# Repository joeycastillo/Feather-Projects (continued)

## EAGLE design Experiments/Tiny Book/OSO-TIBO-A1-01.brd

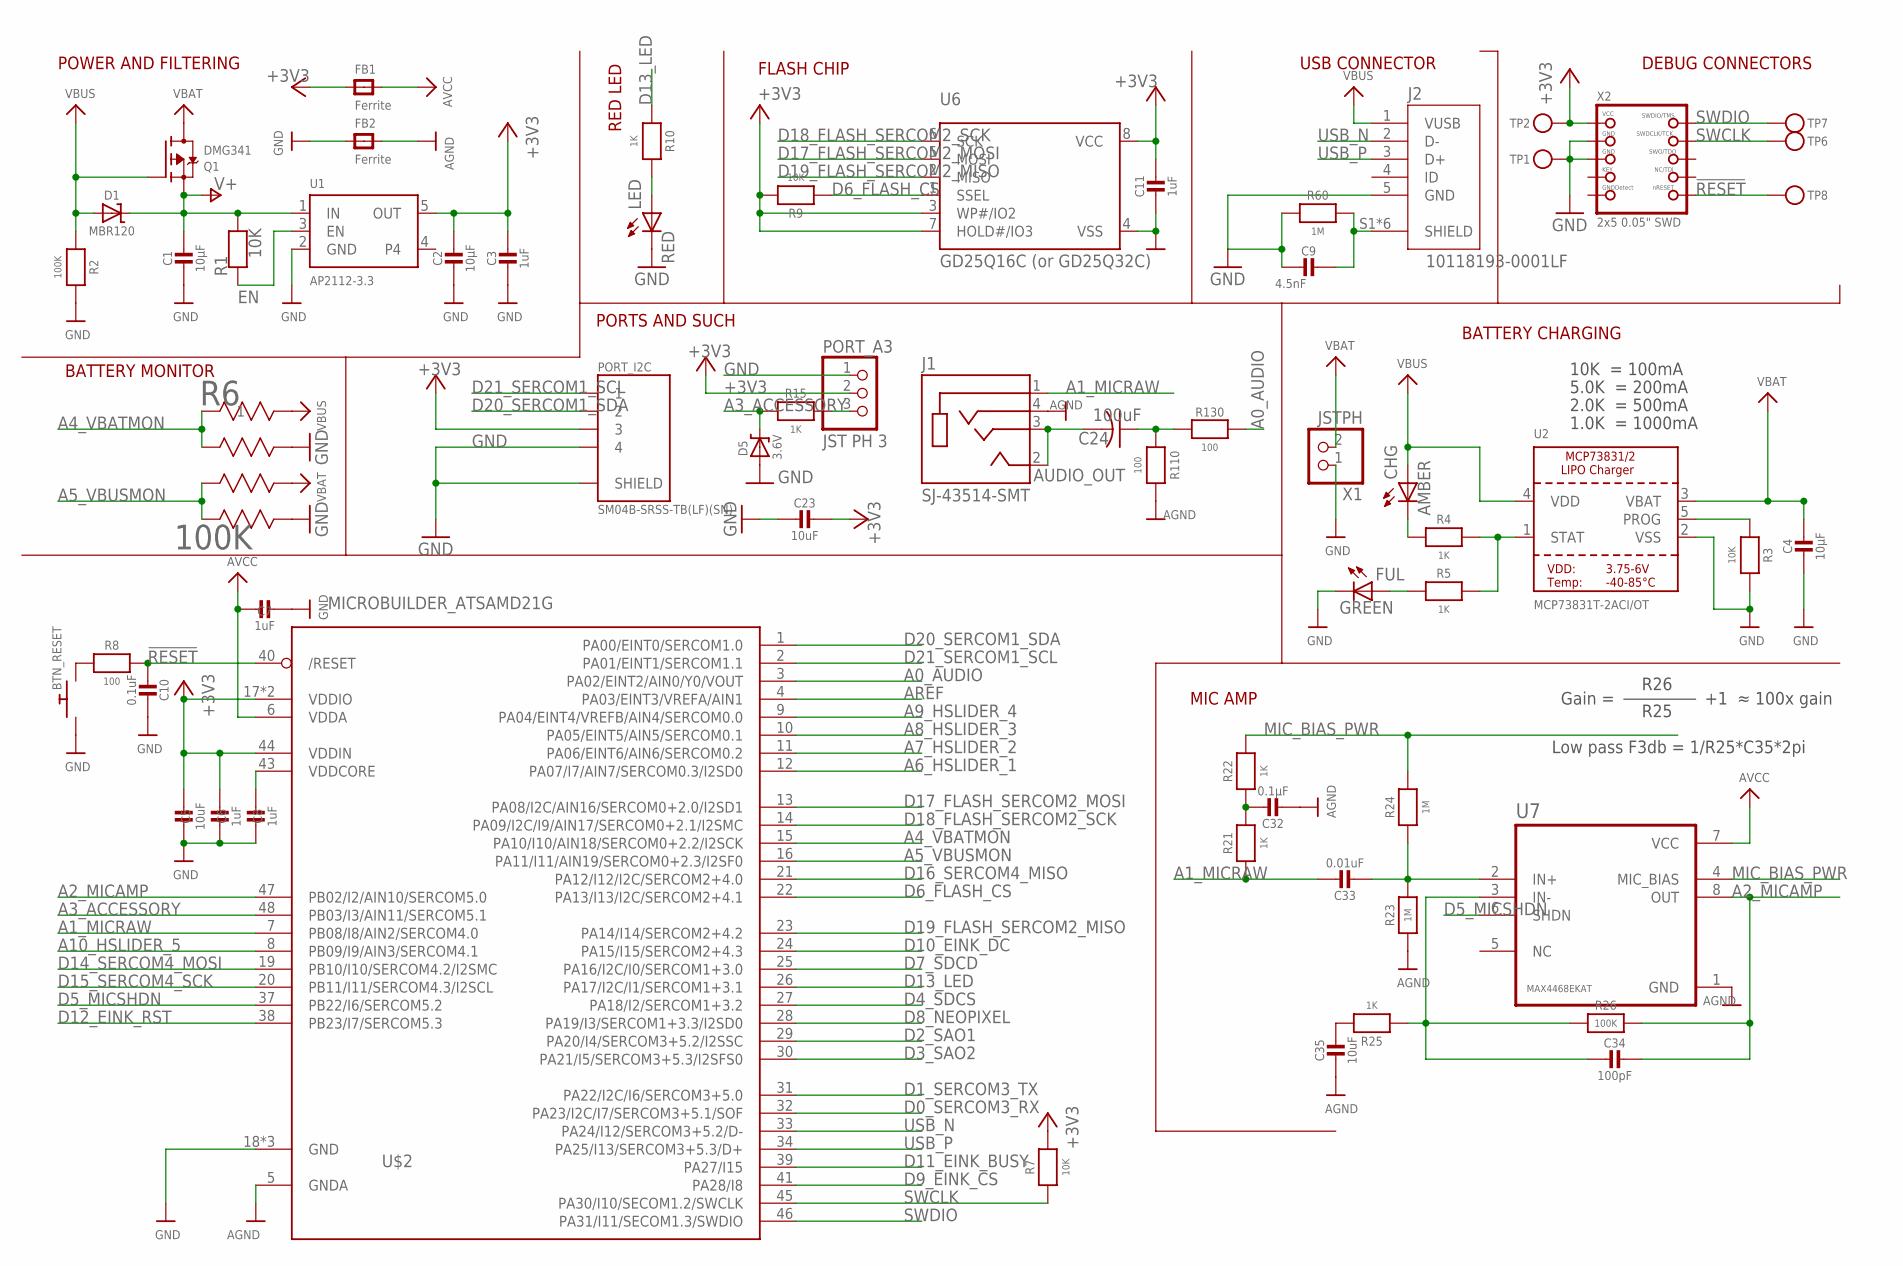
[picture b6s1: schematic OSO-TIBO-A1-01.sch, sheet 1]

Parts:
BTN_RESET: SPST_TACTILE_SWITCHRA-THRU; MJTP1117
C1, C2, C4: 10µF; 0805-NO
C3, C6, C7, C8: 1uF; 0805-NO
C5: 10uF; 0805_10MGAP
C9: 4.5nF; 0805-NO
C10: 0.1uF; 0805_10MGAP
C11: 1uF; 0805_10MGAP
C23, C35: 10uF; 0805-NO
C24: 100uF; C1210
C32: 0.1µF; 0805-NO
C33: 0.01uF; 0805-NO
C34: 100pF; 0805-NO
CHG: AMBER; CHIP-LED0805
D1: MBR120; SOD-123
D5: 3.6V; SOD-123
FB1, FB2: Ferrite; 0805
FUL: GREEN; CHIP-LED0805
J1: SJ-43514-SMT; CUI_SJ-43514-SMT
J2: 10118193-0001LF; FCI_10118193-0001LF
LED: RED; CHIP-LED0805
PORT_A3: JST PH 3; JSTPH3
PORT_I2C: SM04B-SRSS-TB(LF)(SN); JST_SM04B-SRSS-TB(LF)(SN)
Q1: DMG341; SOT23-R
R1, R3, R7, R9: 10K; 0805-NO
R2, R26: 100K; 0805-NO
R4, R5, R10, R21, R22, R25: 1K; 0805-NO
R6: 100K; EXBV8V
R8: 100; 0805_10MGAP
R15: 1K; _0805MP
R23, R24, R60: 1M; 0805-NO
R110, R130: 100; 0805-NO
TP1, TP2, TP6, TP7, TP8: TESTPOINTROUND2MMNO; TESTPOINT_ROUND_2MM_NO
U1: AP2112-3.3; SOT23-5
U2: MCP73831T-2ACI/OT; SOT23-5
U6: GD25Q16C (or GD25Q32C); MICROBUILDER_SOIC8_150MIL
U7: MAX4468EKAT; SOT65P280X145-8N
U$2: MICROBUILDER_ATSAMD21G; QFP50P900X900X120-48N
X1: JSTPH; JSTPH2
X2: 2x5 0.05" SWD; 2X05_1.27MM_BOX_POSTS

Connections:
!RESET: C10.2, R8.2, TP8.P$1, U$2.40 (/RESET), X2.10 (NRESET)
+3V3: C2.1, C3.1, C5.1, C6.1, C11.1, C23.1, FB1.1, PORT_A3.2, PORT_I2C.3, R7.2, R9.2, TP2.P$1, U1.5 (OUT), U6.3 (WP#/IO2), U6.7 (HOLD#/IO3), U6.8 (VCC), U$2.17 (VDDIO), U$2.36 (VDDIO), U$2.44 (VDDIN), X2.1 (VCC); also elsewhere on the board
A0_AUDIO: R130.1, U$2.3 (PA02/EINT2/AIN0/Y0/VOUT)
A1_MICRAW: C33.1, J1.1 (SLEEVE), R21.1, U$2.7 (PB08/I8/AIN2/SERCOM4.0)
A2_MICAMP: C34.1, R26.2, U7.8 (OUT), U$2.47 (PB02/I2/AIN10/SERCOM5.0)
A3_ACCESSORY: D5.C, R15.2, U$2.48 (PB03/I3/AIN11/SERCOM5.1)
A4_VBATMON: R6.1, R6.2, U$2.15 (PA10/I10/AIN18/SERCOM0+2.2/I2SCK)
A5_VBUSMON: R6.3, R6.4, U$2.16 (PA11/I11/AIN19/SERCOM0+2.3/I2SF0)
A6_HSLIDER_1: U$2.12 (PA07/I7/AIN7/SERCOM0.3/I2SD0); also elsewhere on the board
A7_HSLIDER_2: U$2.11 (PA06/EINT6/AIN6/SERCOM0.2); also elsewhere on the board
A8_HSLIDER_3: U$2.10 (PA05/EINT5/AIN5/SERCOM0.1); also elsewhere on the board
A9_HSLIDER_4: U$2.9 (PA04/EINT4/VREFB/AIN4/SERCOM0.0); also elsewhere on the board
A10_HSLIDER_5: U$2.8 (PB09/I9/AIN3/SERCOM4.1); also elsewhere on the board
AGND: C32.2, C35.2, FB2.2, J1.4 (RING2), R23.1, R110.1, U7.1 (GND), U$2.5 (GNDA)
AREF: U$2.4 (PA03/EINT3/VREFA/AIN1)
AUDIO_OUT: C24.2, J1.2 (TIP), J1.3 (RING1)
AVCC: C7.2, FB1.2, U7.7 (VCC), U$2.6 (VDDA)
D0_SERCOM3_RX: U$2.32 (PA23/I2C/I7/SERCOM3+5.1/SOF); also elsewhere on the board
D1_SERCOM3_TX: U$2.31 (PA22/I2C/I6/SERCOM3+5.0); also elsewhere on the board
D2_SAO1: U$2.29 (PA20/I4/SERCOM3+5.2/I2SSC)
D3_SAO2: U$2.30 (PA21/I5/SERCOM3+5.3/I2SFS0)
D4_SDCS: U$2.27 (PA18/I2/SERCOM1+3.2); also elsewhere on the board
D5_MICSHDN: U7.6 (SHDN), U$2.37 (PB22/I6/SERCOM5.2)
D6_FLASH_CS: R9.1, U6.1 (SSEL), U$2.22 (PA13/I13/I2C/SERCOM2+4.1)
D7_SDCD: U$2.25 (PA16/I2C/I0/SERCOM1+3.0); also elsewhere on the board
D8_NEOPIXEL: U$2.28 (PA19/I3/SERCOM1+3.3/I2SD0); also elsewhere on the board
D9_EINK_CS: U$2.41 (PA28/I8); also elsewhere on the board
D10_EINK_DC: U$2.24 (PA15/I15/SERCOM2+4.3); also elsewhere on the board
D11_EINK_BUSY: U$2.39 (PA27/I15); also elsewhere on the board
D12_EINK_RST: U$2.38 (PB23/I7/SERCOM5.3); also elsewhere on the board
D13_LED: R10.1, U$2.26 (PA17/I2C/I1/SERCOM1+3.1)
D14_SERCOM4_MOSI: U$2.19 (PB10/I10/SERCOM4.2/I2SMC); also elsewhere on the board
D15_SERCOM4_SCK: U$2.20 (PB11/I11/SERCOM4.3/I2SCL); also elsewhere on the board
D16_SERCOM4_MISO: U$2.21 (PA12/I12/I2C/SERCOM2+4.0); also elsewhere on the board
D17_FLASH_SERCOM2_MOSI: U6.5 (MOSI), U$2.13 (PA08/I2C/AIN16/SERCOM0+2.0/I2SD1)
D18_FLASH_SERCOM2_SCK: U6.6 (SCK), U$2.14 (PA09/I2C/I9/AIN17/SERCOM0+2.1/I2SMC)
D19_FLASH_SERCOM2_MISO: U6.2 (MISO), U$2.23 (PA14/I14/SERCOM2+4.2)
D20_SERCOM1_SDA: PORT_I2C.2, U$2.1 (PA00/EINT0/SERCOM1.0)
D21_SERCOM1_SCL: PORT_I2C.1, U$2.2 (PA01/EINT1/SERCOM1.1)
EN: R1.1, U1.3 (EN); also elsewhere on the board
GND: BTN_RESET.P$1, C1.2, C2.2, C3.2, C4.2, C5.2, C6.2, C7.1, C8.2, C9.2, C10.1, C11.2, C23.2, D5.A, FB2.1, FUL.C, J2.5 (GND), LED.C, PORT_A3.1, PORT_I2C.4, PORT_I2C.S1 (SHIELD), PORT_I2C.S2 (SHIELD), R2.2, R3.2, R6.5, R6.7, R60.2, TP1.P$1, U1.2 (GND), U2.2 (VSS), U6.4 (VSS), U$2.18 (GND), U$2.35 (GND), U$2.42 (GND), X1.1, X2.3 (GND), X2.5 (GND); also elsewhere on the board
MIC_BIAS_PWR: R22.2, R24.2, U7.4 (MIC_BIAS)
unnamed: BTN_RESET.P$2, R8.1
unnamed: CHG.C, R4.1
unnamed: C24.1, R110.2, R130.2
unnamed: LED.A, R10.2
unnamed: FUL.A, R5.1
unnamed: C32.1, R21.2, R22.1
unnamed: C33.2, R23.2, R24.1, U7.2 (IN+)
unnamed: C34.2, R25.1, R26.1, U7.3 (IN-)
unnamed: C35.1, R25.2
PROG: R3.1, U2.5 (PROG)
SHIELD: C9.1, J2.S1 (SHIELD), J2.S2 (SHIELD), J2.S3 (SHIELD), J2.S4 (SHIELD), J2.S5 (SHIELD), J2.S6 (SHIELD), R60.1
STAT: R4.2, R5.2, U2.1 (STAT)
SWCLK: R7.1, TP6.P$1, U$2.45 (PA30/I10/SECOM1.2/SWCLK), X2.4 (SWDCLK)
SWDIO: TP7.P$1, U$2.46 (PA31/I11/SECOM1.3/SWDIO), X2.2 (SWDIO)
USB_N: J2.2 (D-), U$2.33 (PA24/I12/SERCOM3+5.2/D-)
USB_P: J2.3 (D+), U$2.34 (PA25/I13/SERCOM3+5.3/D+)
V+: C1.1, D1.C, Q1.2 (S), R1.2, U1.1 (IN)
VBAT: C4.1, Q1.3 (D), R6.6, U2.3 (VBAT), X1.2
VBUS: CHG.A, D1.A, J2.1 (VUSB), Q1.1 (G), R2.1, R6.8, U2.4 (VDD)
VDDCORE: C8.1, U$2.43 (VDDCORE)
_ACCESSORY: PORT_A3.3, R15.1

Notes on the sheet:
POWER AND FILTERING
10K = 100mA
5.0K = 200mA
2.0K = 500mA
1.0K = 1000mA
BATTERY CHARGING
DEBUG CONNECTORS
USB CONNECTOR
BATTERY MONITOR
FLASH CHIP
RED LED
Gain =
R26
R25
≈ 100x gain
Low pass F3db = 1/R25*C35*2pi
PORTS AND SUCH
MIC AMP

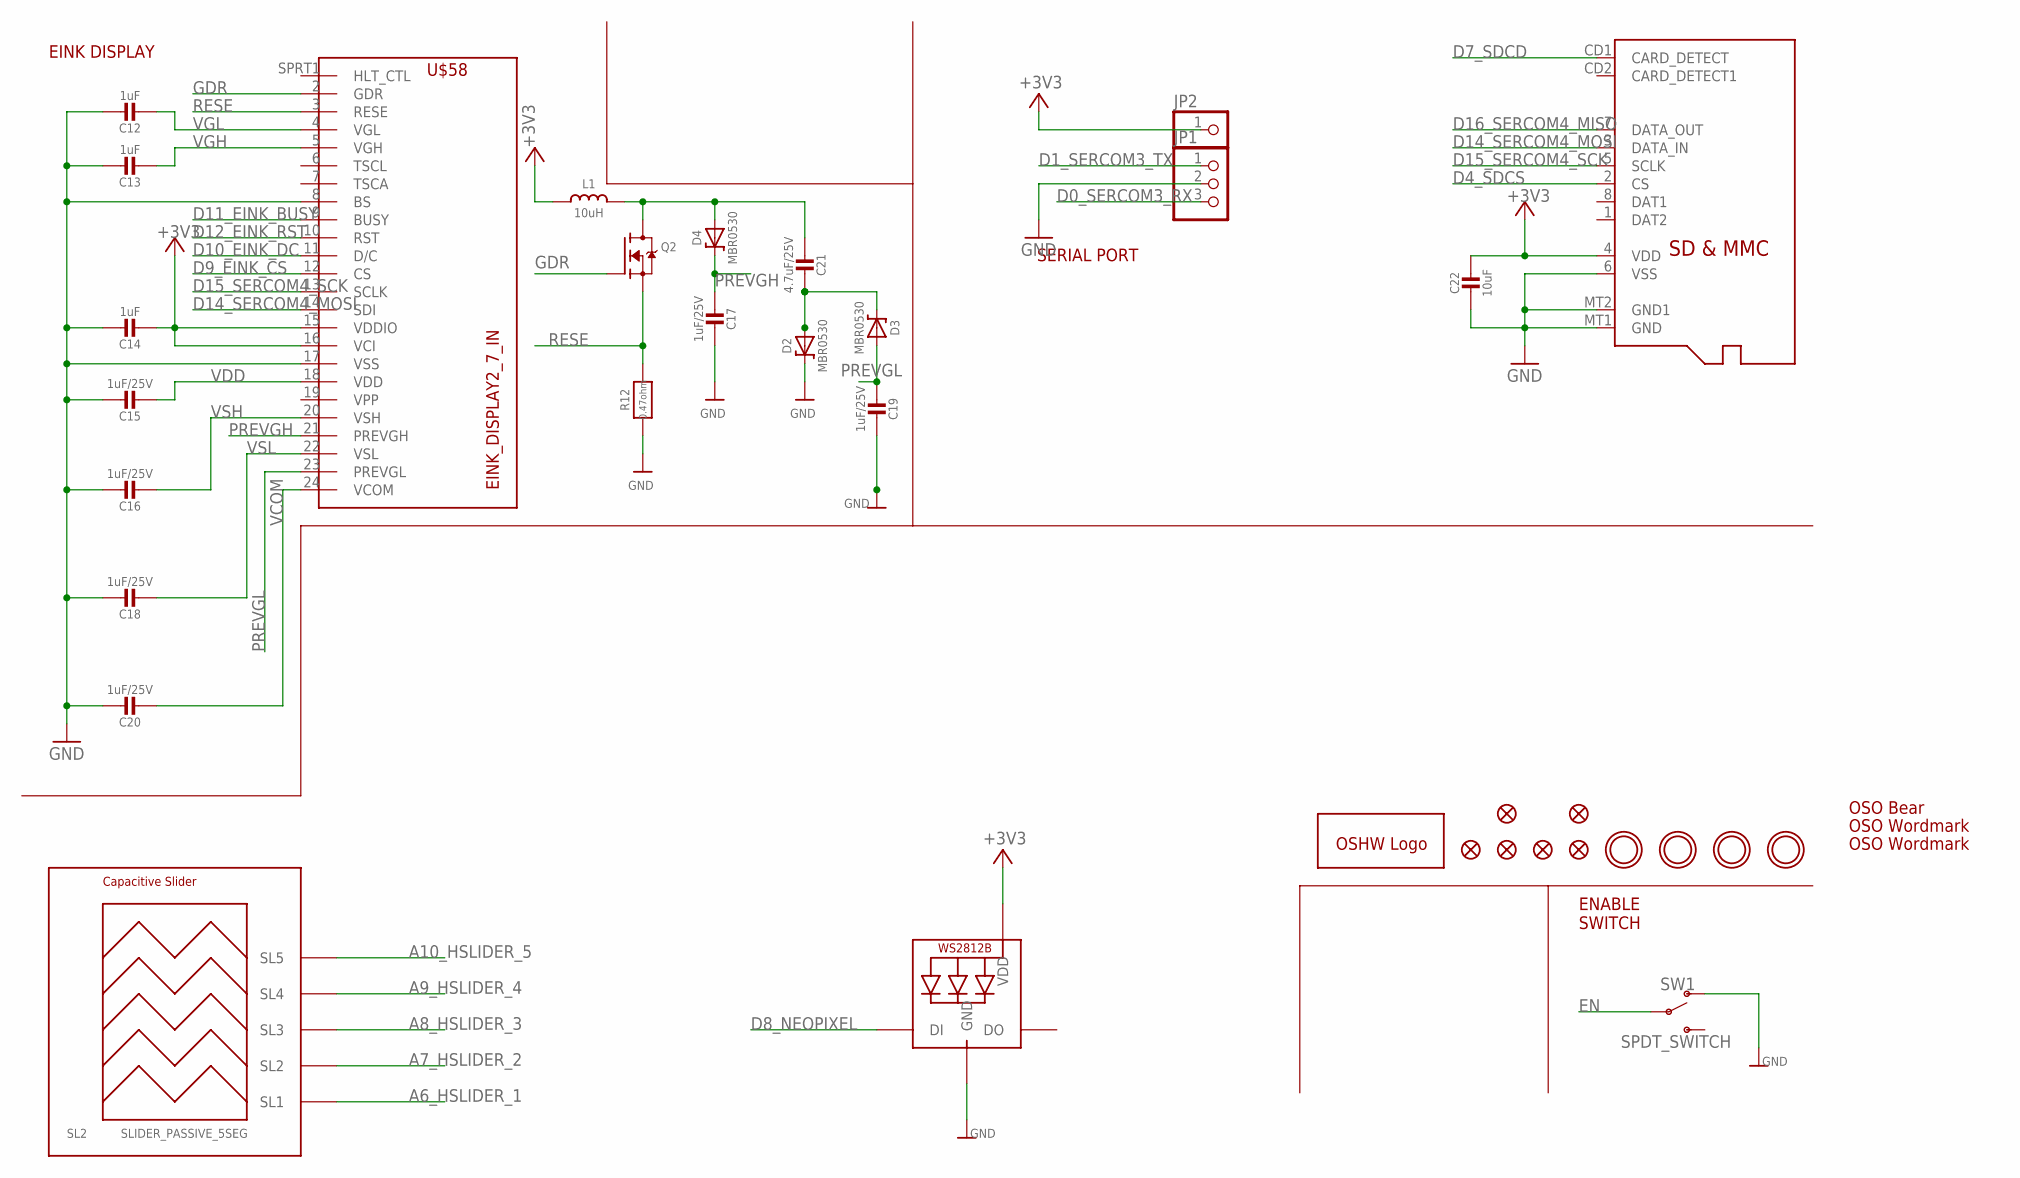
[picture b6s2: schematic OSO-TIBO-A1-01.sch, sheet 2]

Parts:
C12, C13, C14: 1uF; 0805_10MGAP
C15, C16, C17, C18, C19, C20: 1uF/25V; 0805_10MGAP
C21: 4.7uF/25V; 0805-NO
C22: 10uF; 0805_10MGAP
D2, D3, D4: MBR0530; SOD-123
D8_NEOPIXEL: WS2812B_4020
FID1, FID2, FID3, FID4, FID5, FID6: FIDUCIAL_1MM
GOLD_ORB_SM1: OSHWLOGOLOGO5MM; OSHW_5MM
JP1: PINHD-1X3; 1X03
JP2: PINHD-1X1; 1X01
L1: 10uH; INDUCTOR_4X4MM_NR401
MICROSD: MICROSD
Q2: IRLML0100; SOT23-3
R12: 0.47ohm; 0805_10MGAP
SL2: SLIDER_PASSIVE_5SEG; SLIDER_PASSIVE_5SEG_12MM
SW1: SPDT_SWITCH; A10767
U$1, U$4, U$5, U$7: MOUNTINGHOLE2.5; MOUNTINGHOLE_2.5_PLATED
U$45: OSO_BEAR; OSO_BEAR_750MIL
U$47: OSO_TEXT; OSO_TEXT_435MIL
U$48: OSO_TEXTOSO_TEXT_ONELINE_125MIL; OSO_ONELINE_125MIL
U$58: EINK_DISPLAY2_7_IN; EINK_DISPLAY_2_7_IN

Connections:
+3V3: C14.2, C22.1, D8_NEOPIXEL.2 (VDD), JP2.1, L1.P$2 (2), MICROSD.4 (VDD), U$58.15 (VDDIO), U$58.16 (VCI); also elsewhere on the board
A6_HSLIDER_1: SL2.SL1; also elsewhere on the board
A7_HSLIDER_2: SL2.SL2; also elsewhere on the board
A8_HSLIDER_3: SL2.SL3; also elsewhere on the board
A9_HSLIDER_4: SL2.SL4; also elsewhere on the board
A10_HSLIDER_5: SL2.SL5; also elsewhere on the board
D0_SERCOM3_RX: JP1.3; also elsewhere on the board
D1_SERCOM3_TX: JP1.1; also elsewhere on the board
D4_SDCS: MICROSD.2 (CS); also elsewhere on the board
D7_SDCD: MICROSD.CD1 (CARD_DETECT); also elsewhere on the board
D8_NEOPIXEL: D8_NEOPIXEL.1 (DI); also elsewhere on the board
D9_EINK_CS: U$58.12 (CS); also elsewhere on the board
D10_EINK_DC: U$58.11 (D/C); also elsewhere on the board
D11_EINK_BUSY: U$58.9 (BUSY); also elsewhere on the board
D12_EINK_RST: U$58.10 (RST); also elsewhere on the board
D14_SERCOM4_MOSI: MICROSD.3 (DATA_IN), U$58.14 (SDI); also elsewhere on the board
D15_SERCOM4_SCK: MICROSD.5 (SCLK), U$58.13 (SCLK); also elsewhere on the board
D16_SERCOM4_MISO: MICROSD.7 (DATA_OUT); also elsewhere on the board
EN: SW1.P$2; also elsewhere on the board
GDR: Q2.1 (G), U$58.2 (GDR)
GND: C12.1, C13.1, C14.1, C15.1, C16.1, C17.2, C18.1, C19.2, C20.1, C22.2, D2.C, D8_NEOPIXEL.4 (GND), JP1.2, MICROSD.6 (VSS), MICROSD.MT1 (GND), MICROSD.MT2 (GND1), R12.2, SW1.P$1 (O), U$58.8 (BS), U$58.17 (VSS); also elsewhere on the board
unnamed: C21.2, D2.A, D3.C
unnamed: C21.1, D4.A, L1.P$1 (1), Q2.3 (D)
PREVGH: C17.1, D4.C, U$58.21 (PREVGH)
PREVGL: C19.1, D3.A, U$58.23 (PREVGL)
RESE: Q2.2 (S), R12.1, U$58.3 (RESE)
VCOM: C20.2, U$58.24 (VCOM)
VDD: C15.2, U$58.18 (VDD)
VGH: C13.2, U$58.5 (VGH)
VGL: C12.2, U$58.4 (VGL)
VSH: C16.2, U$58.20 (VSH)
VSL: C18.2, U$58.22 (VSL)

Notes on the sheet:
EINK DISPLAY
ENABLE SWITCH
SERIAL PORT

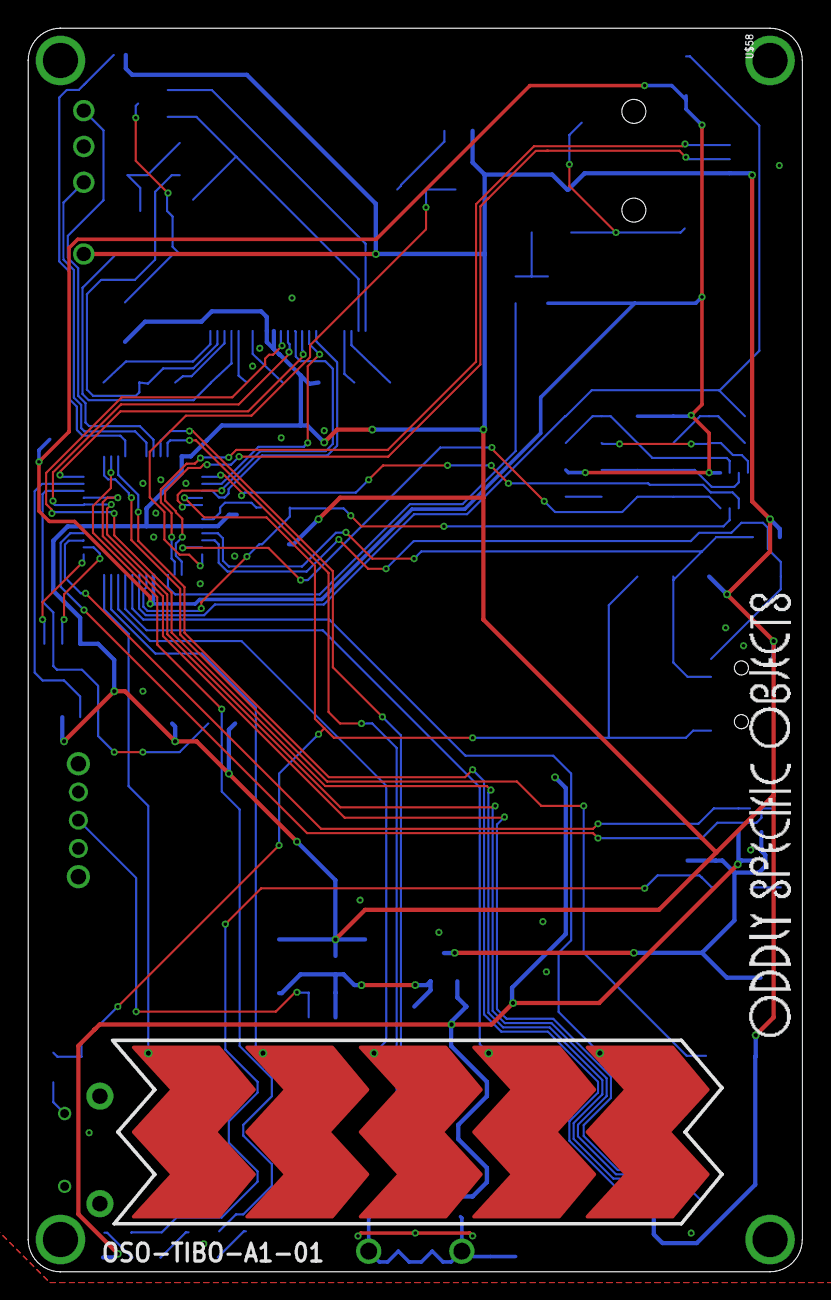
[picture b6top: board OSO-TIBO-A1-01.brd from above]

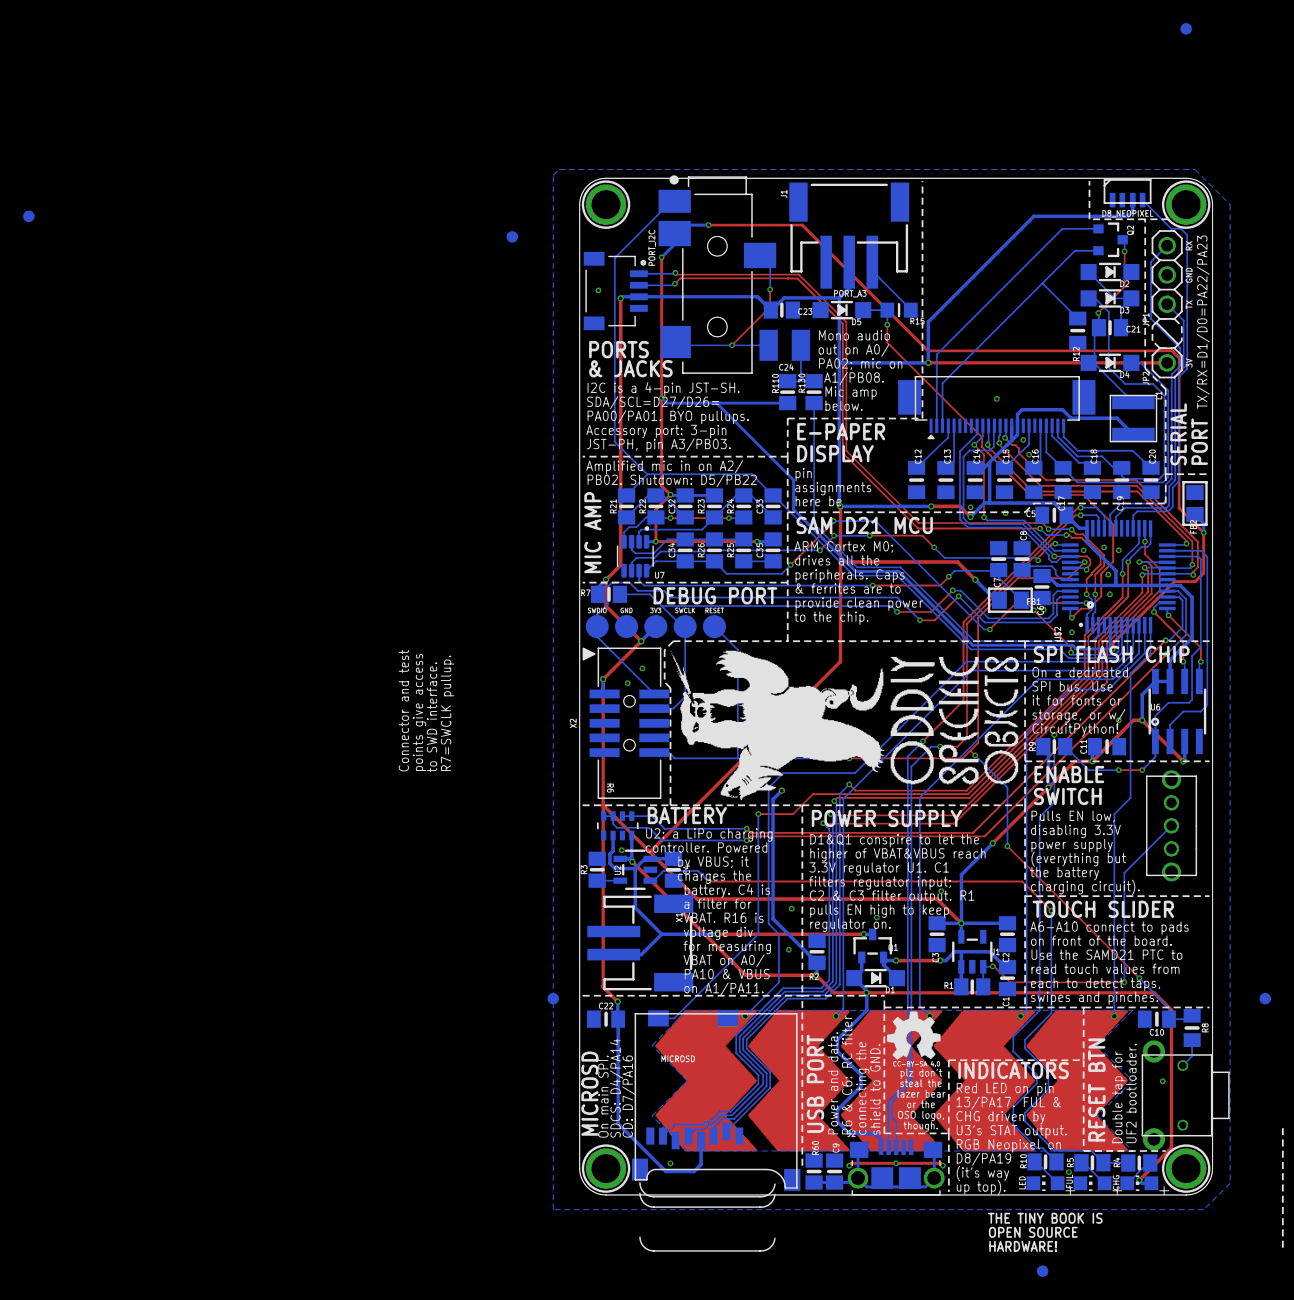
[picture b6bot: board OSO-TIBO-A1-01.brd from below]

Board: 2 copper layers, 54.9 x 88.1 mm, 100 parts (97 on the bottom side), 72 nets.
